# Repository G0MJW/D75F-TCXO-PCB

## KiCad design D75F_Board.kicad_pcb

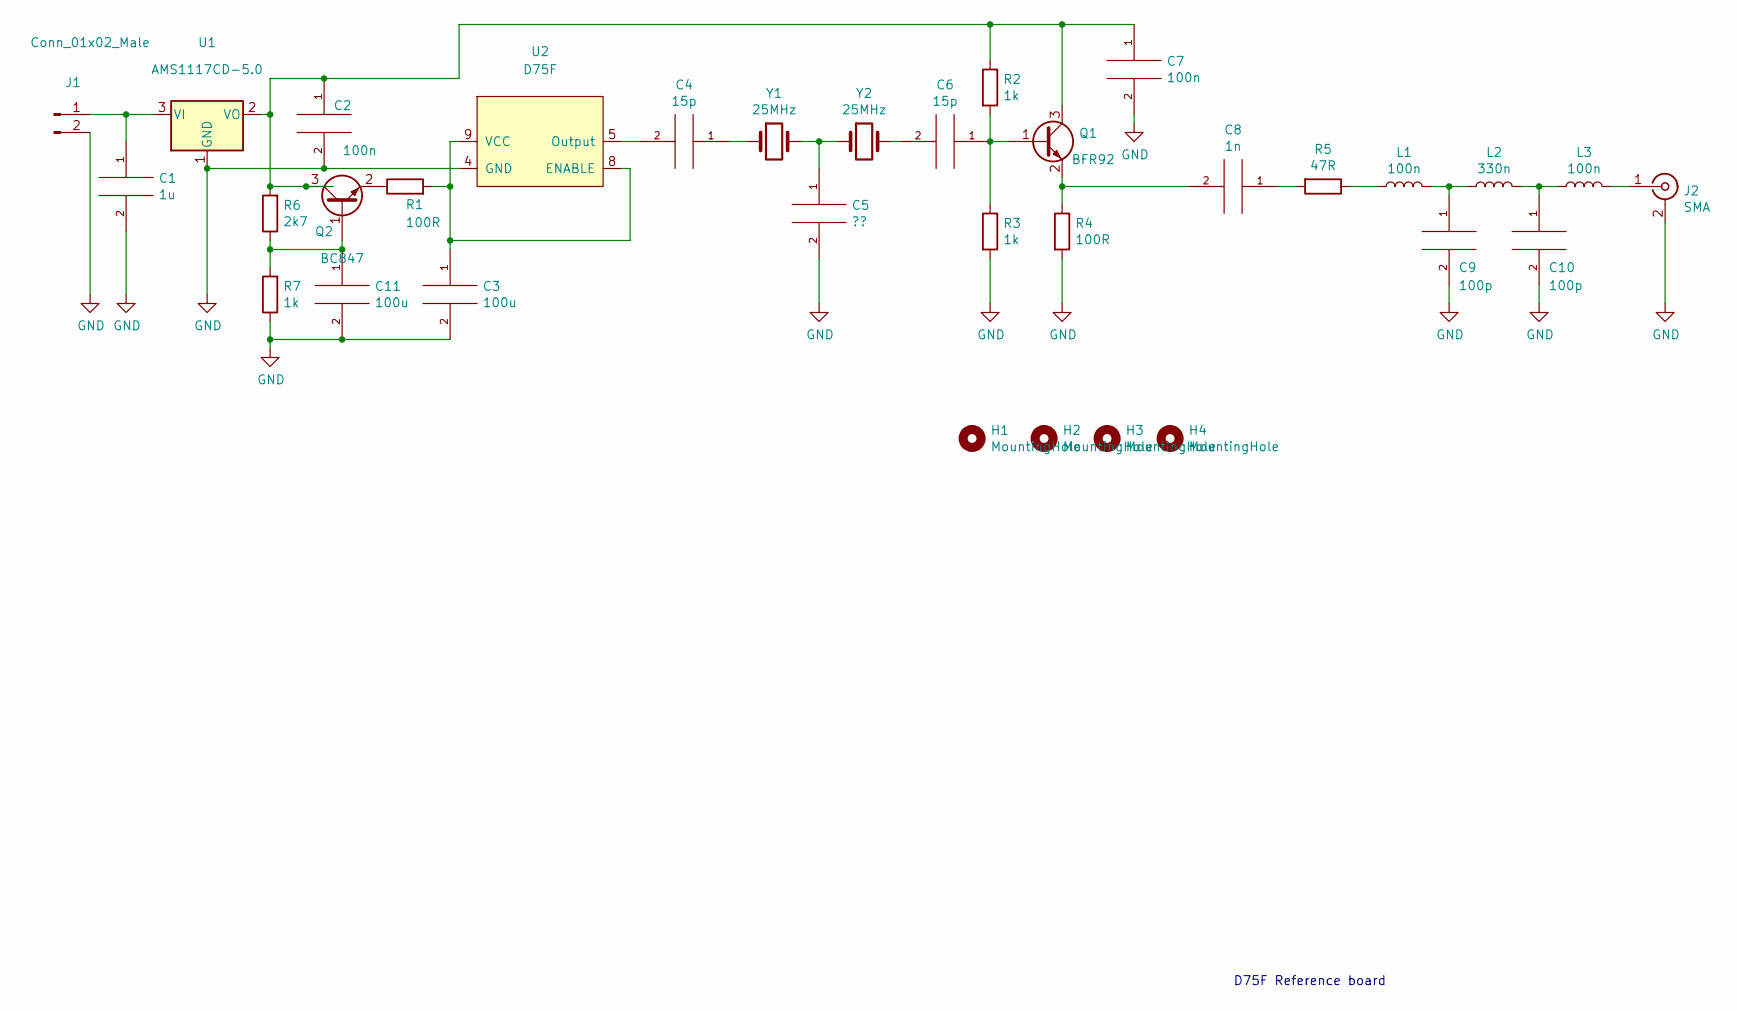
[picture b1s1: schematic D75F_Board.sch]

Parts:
C1: 1u; C_1210_3225Metric_Pad1.42x2.65mm_HandSolder
C2, C7: 100n; C_0805_2012Metric_Pad1.15x1.40mm_HandSolder
C3, C11: 100u; C_1210_3225Metric_Pad1.42x2.65mm_HandSolder
C4, C6: 15p; C_0805_2012Metric_Pad1.15x1.40mm_HandSolder
C5: ??; C_0805_2012Metric_Pad1.15x1.40mm_HandSolder
C8: 1n; C_0805_2012Metric_Pad1.15x1.40mm_HandSolder
C9, C10: 100p; C_0805_2012Metric_Pad1.15x1.40mm_HandSolder
H1, H2, H3, H4: MountingHole; MountingHole_2.7mm_M2.5
J1: Conn_01x02_Male; Molex_KK-254_AE-6410-02A_1x02_P2.54mm_Vertical
J2: SMA; SMA_Amphenol_901-144_Vertical
L1, L3: 100n; L_1812_4532Metric_Pad1.30x3.40mm_HandSolder
L2: 330n; L_1812_4532Metric_Pad1.30x3.40mm_HandSolder
Q1: BFR92; SOT-323_SC-70
Q2: BC847; SOT-23
R1, R4: 100R; R_0805_2012Metric_Pad1.15x1.40mm_HandSolder
R2, R3, R7: 1k; R_0805_2012Metric_Pad1.15x1.40mm_HandSolder
R5: 47R; R_0805_2012Metric_Pad1.15x1.40mm_HandSolder
R6: 2k7; R_0805_2012Metric_Pad1.15x1.40mm_HandSolder
U1: AMS1117CD-5.0; TO-252-3_TabPin2
U2: D75F
Y1, Y2: 25MHz; Crystal_HC49-U_Vertical

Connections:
GND: C1.2, C2.2, C3.2, C5.2, C7.2, C9.2, C10.2, C11.2, J1.2, J2.2 (Ext), R3.2, R4.2, R7.1, U1.1 (GND), U2.4 (GND)
unnamed: C1.1, J1.1, U1.3 (VI)
unnamed: C2.1, C7.1, Q1.3 (C), Q2.3 (C), R2.1, R6.2, U1.2 (VO)
unnamed: C3.1, R1.2, U2.8 (ENABLE), U2.9 (VCC)
unnamed: C4.1, Y1.1
unnamed: C4.2, U2.5 (Output)
unnamed: C5.1, Y1.2, Y2.1
unnamed: C6.1, Q1.1 (B), R2.2, R3.1
unnamed: C6.2, Y2.2
unnamed: C8.1, R5.2
unnamed: C8.2, Q1.2 (E), R4.1
unnamed: C9.1, L1.2, L2.1
unnamed: C10.1, L2.2, L3.1
unnamed: C11.1, Q2.1 (B), R6.1, R7.2
unnamed: J2.1 (In), L3.2
unnamed: L1.1, R5.1
unnamed: Q2.2 (E), R1.1

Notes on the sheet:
D75F Reference board

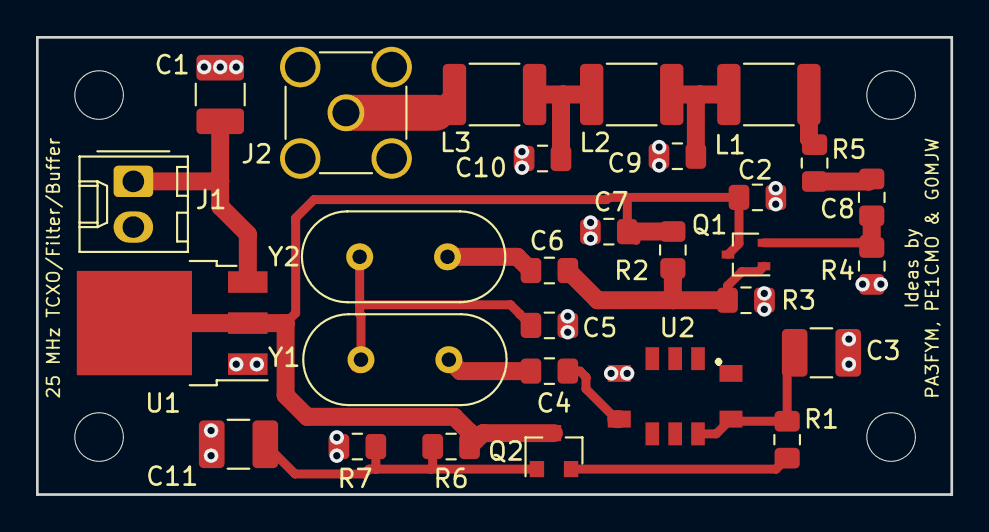
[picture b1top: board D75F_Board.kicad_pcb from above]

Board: 2 copper layers, 50.8 x 25.4 mm, 33 parts (0 on the bottom side), 17 nets.
